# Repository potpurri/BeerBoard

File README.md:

# BeerBoard

**BeerBoard** is a beer-shaped microcontroller breakout board based on the STM32F030C6T6. [Schematic can be found here.](https://github.com/potpurri/BeerBoard/blob/a81b2d54139fa46588d7e338071e49ddc263d606/Schematic_v02.pdf) Originally designed as a trophy for a beer quiz, its primary feature is blinking LEDs, adding a fun, interactive element to the prize. The project also served as an opportunity to experiment with JLCPCB's multicolor silkscreen options.

This board consists of **4 layers**, providing a robust platform for various applications beyond its original purpose. It also includes **breakout pins for I2C, SPI, and USART**, offering versatile connectivity options for external devices and peripherals. Below are images showing the assebled board, different silkscreen options and 3D renderings of the BeerBoard.

The board is soldered by me using a [Pinecil V2](https://wiki.pine64.org/wiki/Pinecil) by PINE64  and [MHP50](https://e-design.com.cn/en/Mini-Hot-Plate-Preheater-MHP50-PG9555615) by MiniWare.

## Features
- Beer-shaped PCB design
- STM32F030C6T6 microcontroller at its core
- Blinking LEDs for visual effects
- 4-layer PCB
- Available in both multicolor and regular silkscreen versions

## Images

### Assembled board

### PCBs

### 3D Renderings & Schematic

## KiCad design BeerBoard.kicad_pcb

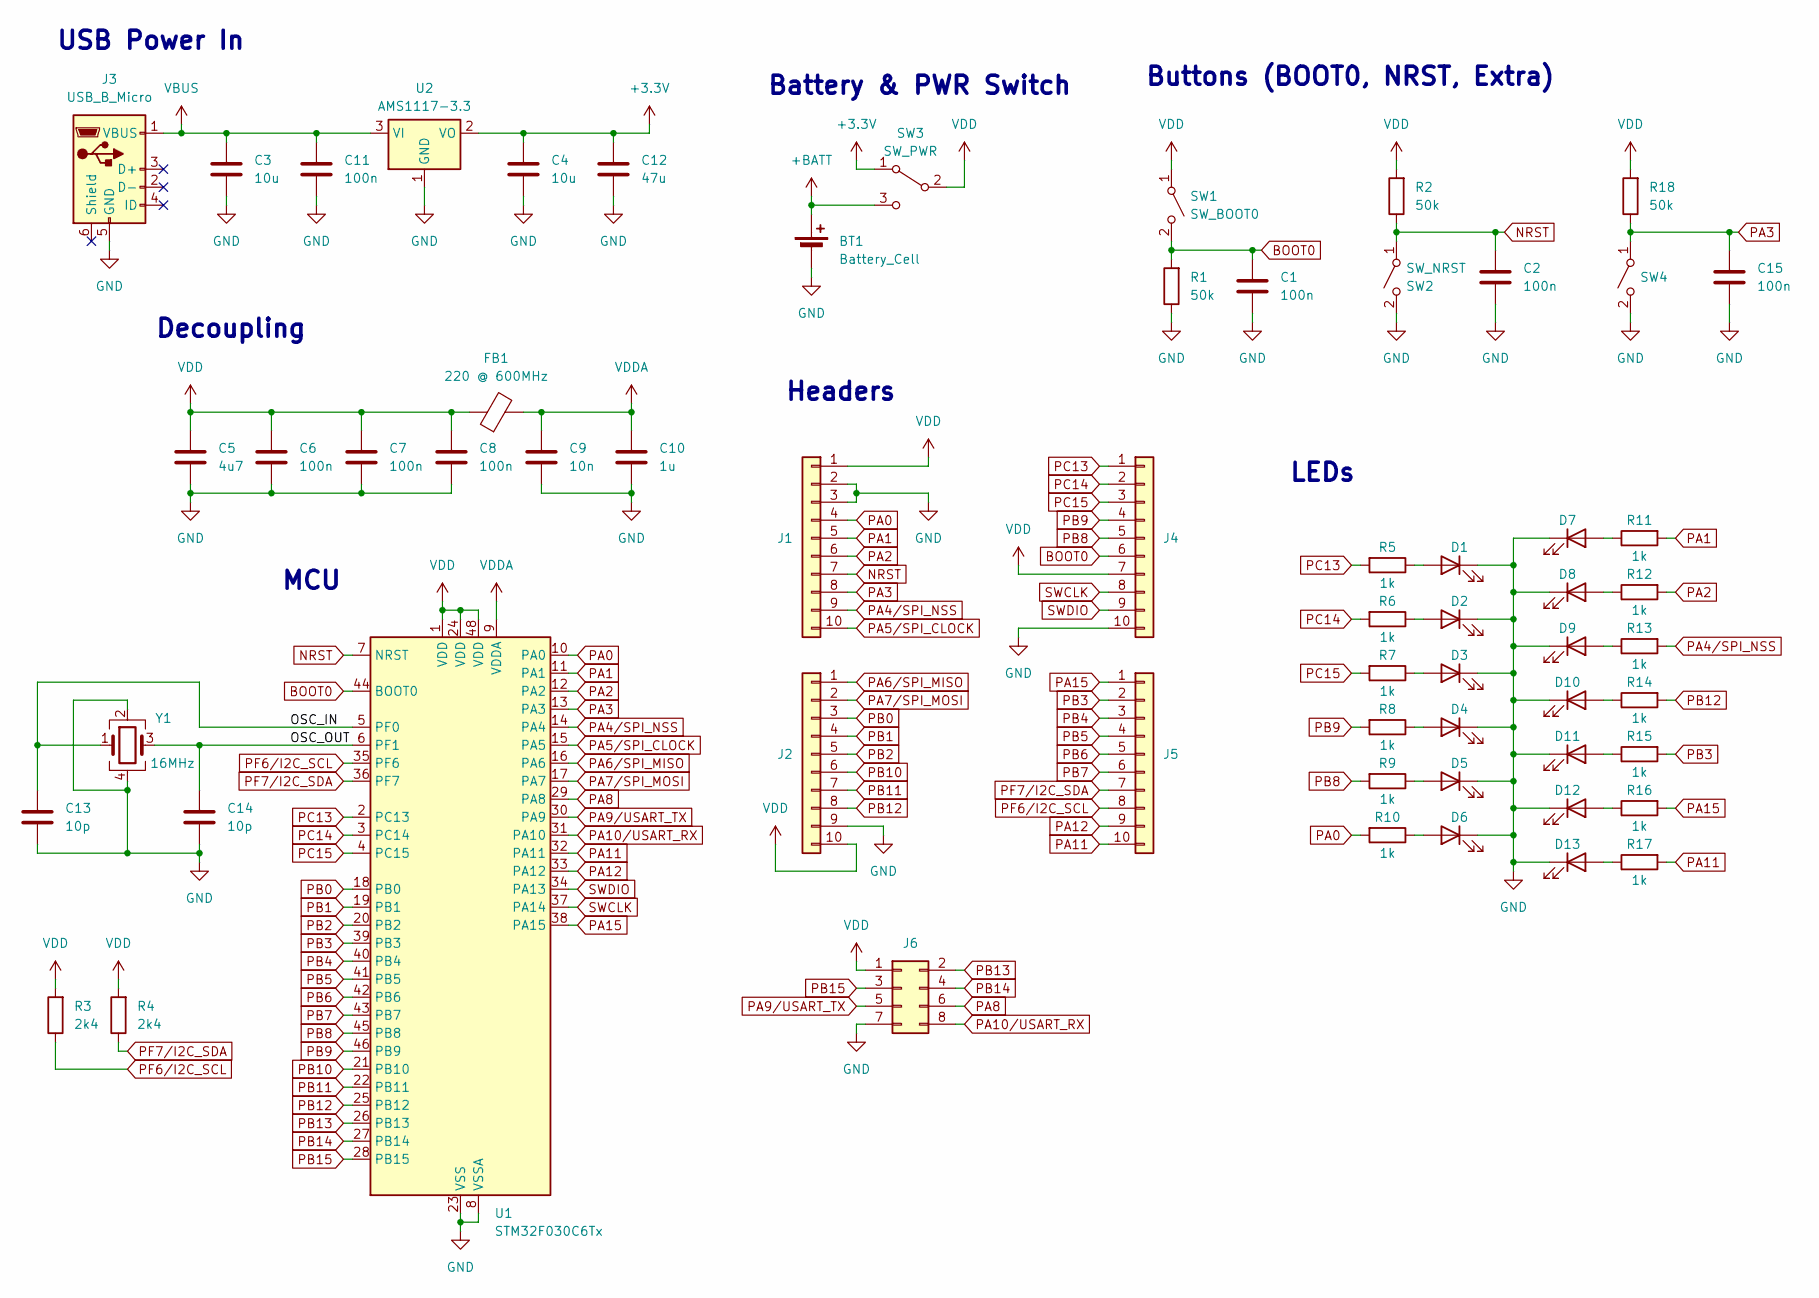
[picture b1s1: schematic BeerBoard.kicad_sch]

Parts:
BT1: Battery_Cell; CoinCell CR2032
C1, C2, C6, C7, C8, C11, C15: 100n; C_0603_1608Metric
C3, C4: 10u; C_0805_2012Metric
C5: 4u7; C_0805_2012Metric
C9: 10n; C_0603_1608Metric
C10: 1u; C_0805_2012Metric
C12: 47u; C_1206_3216Metric
C13, C14: 10p; C_0603_1608Metric
D1, D2, D3, D4, D5, D6, D7, D8, D9, D10, D11, D12, D13: LED; LED_0805_2012Metric_Pad1.15x1.40mm_HandSolder
FB1: 220 @ 600MHz; L_0805_2012Metric
J1, J2, J4, J5: Conn_01x10; PinHeader_1x10_P2.54mm_Vertical
J3: USB_B_Micro; USB_Micro-B_Wuerth_629105150521
J6: Conn_02x04_Odd_Even; PinHeader_2x04_P2.54mm_Vertical
R1, R2, R18: 50k; R_0805_2012Metric
R3, R4: 2k4; R_0805_2012Metric
R5, R6, R7, R8, R9, R10, R11, R12, R13, R14, R15, R16, R17: 1k; R_0603_1608Metric
SW1: SW_BOOT0; 3mm x 4mm micro switch button
SW2, SW4: SW_NRST; 3mm x 4mm micro switch button
SW3: SW_PWR; Schiebeschalter SS-12D00
U1: STM32F030C6Tx; LQFP-48_7x7mm_P0.5mm
U2: AMS1117-3.3; SOT-223-3_TabPin2
Y1: 16MHz; Crystal_SMD_3225-4Pin_3.2x2.5mm

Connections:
+3.3V: C4.1, C12.1, SW3.1 (A), U2.2 (VO)
+BATT: BT1.1 (+), SW3.3 (C)
/OSC_IN: C13.1, U1.5 (PF0), Y1.1
/OSC_OUT: C14.1, U1.6 (PF1), Y1.3
BOOT0: C1.1, J4.6, R1.2, SW1.2 (B), U1.44 (BOOT0)
GND: BT1.2 (-), C1.2, C2.2, C3.2, C4.2, C5.2, C6.2, C7.2, C8.2, C9.2, C10.2, C11.2, C12.2, C13.2, C14.2, C15.2, D1.1 (K), D2.1 (K), D3.1 (K), D4.1 (K), D5.1 (K), D6.1 (K), D7.1 (K), D8.1 (K), D9.1 (K), D10.1 (K), D11.1 (K), D12.1 (K), D13.1 (K), J1.2, J1.3, J2.9, J3.5 (GND), J4.10, J6.7, R1.1, SW2.2 (B), SW4.2 (B), U1.8 (VSSA), U1.23 (VSS), U1.47 (VSS), U2.1 (GND), Y1.2, Y1.4
NRST: C2.1, J1.7, R2.1, SW2.1 (A), U1.7 (NRST)
unnamed: D1.2 (A), R5.1
unnamed: D2.2 (A), R6.1
unnamed: D3.2 (A), R7.1
unnamed: D4.2 (A), R8.1
unnamed: D5.2 (A), R9.1
unnamed: D6.2 (A), R10.1
unnamed: D7.2 (A), R11.1
unnamed: D8.2 (A), R12.1
unnamed: D9.2 (A), R13.1
unnamed: D10.2 (A), R14.1
unnamed: D11.2 (A), R15.1
unnamed: D12.2 (A), R16.1
unnamed: D13.2 (A), R17.1
PA0: J1.4, R10.2, U1.10 (PA0)
PA1: J1.5, R11.2, U1.11 (PA1)
PA2: J1.6, R12.2, U1.12 (PA2)
PA3: C15.1, J1.8, R18.1, SW4.1 (A), U1.13 (PA3)
PA4/SPI_NSS: J1.9, R13.2, U1.14 (PA4)
PA5/SPI_CLOCK: J1.10, U1.15 (PA5)
PA6/SPI_MISO: J2.1, U1.16 (PA6)
PA7/SPI_MOSI: J2.2, U1.17 (PA7)
PA8: J6.6, U1.29 (PA8)
PA9/USART_TX: J6.5, U1.30 (PA9)
PA10/USART_RX: J6.8, U1.31 (PA10)
PA11: J5.10, R17.2, U1.32 (PA11)
PA12: J5.9, U1.33 (PA12)
PA15: J5.1, R16.2, U1.38 (PA15)
PB0: J2.3, U1.18 (PB0)
PB1: J2.4, U1.19 (PB1)
PB2: J2.5, U1.20 (PB2)
PB3: J5.2, R15.2, U1.39 (PB3)
PB4: J5.3, U1.40 (PB4)
PB5: J5.4, U1.41 (PB5)
PB6: J5.5, U1.42 (PB6)
PB7: J5.6, U1.43 (PB7)
PB8: J4.5, R9.2, U1.45 (PB8)
PB9: J4.4, R8.2, U1.46 (PB9)
PB10: J2.6, U1.21 (PB10)
PB11: J2.7, U1.22 (PB11)
PB12: J2.8, R14.2, U1.25 (PB12)
PB13: J6.2, U1.26 (PB13)
PB14: J6.4, U1.27 (PB14)
PB15: J6.3, U1.28 (PB15)
PC13: J4.1, R5.2, U1.2 (PC13)
PC14: J4.2, R6.2, U1.3 (PC14)
PC15: J4.3, R7.2, U1.4 (PC15)
PF6/I2C_SCL: J5.8, R3.1, U1.35 (PF6)
PF7/I2C_SDA: J5.7, R4.1, U1.36 (PF7)
SWCLK: J4.8, U1.37 (PA14)
SWDIO: J4.9, U1.34 (PA13)
VBUS: C3.1, C11.1, J3.1 (VBUS), U2.3 (VI)
VDD: C5.1, C6.1, C7.1, C8.1, FB1.1, J1.1, J2.10, J4.7, J6.1, R2.2, R3.2, R4.2, R18.2, SW1.1 (A), SW3.2 (B), U1.1 (VDD), U1.24 (VDD), U1.48 (VDD)
VDDA: C9.1, C10.1, FB1.2, U1.9 (VDDA)

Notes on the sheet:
MCU
Decoupling
USB Power In
Headers
Buttons (BOOT0, NRST, Extra)
LEDs
Battery & PWR Switch

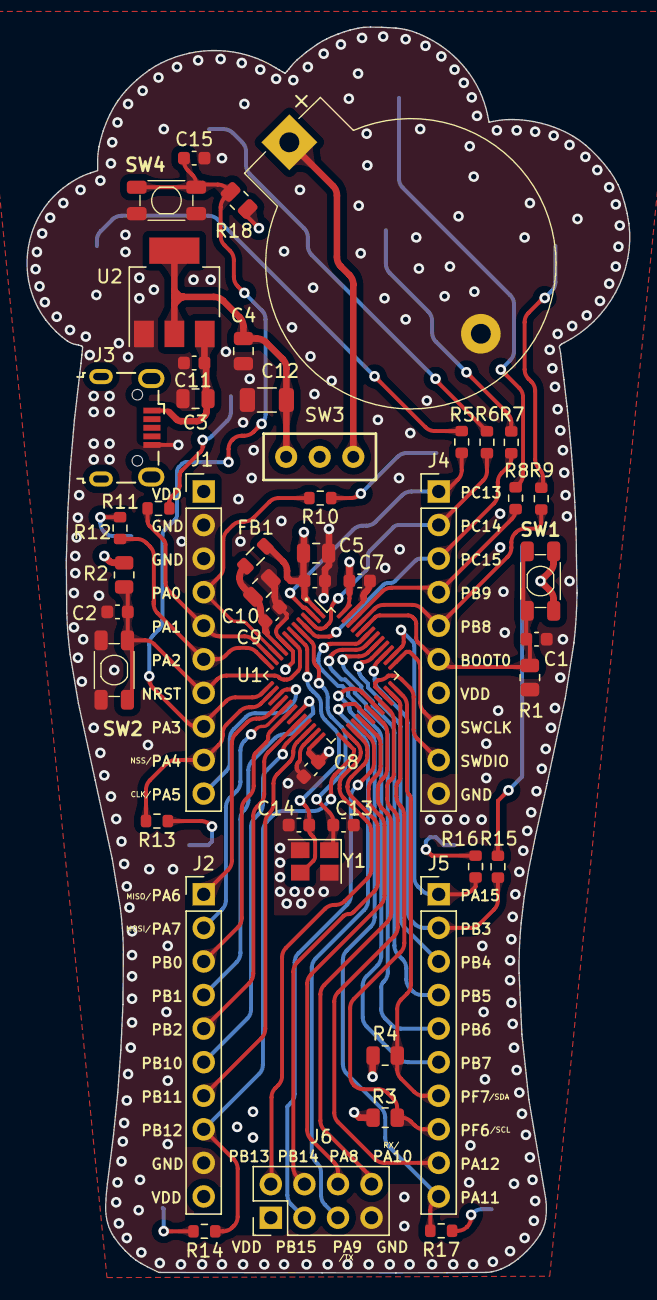
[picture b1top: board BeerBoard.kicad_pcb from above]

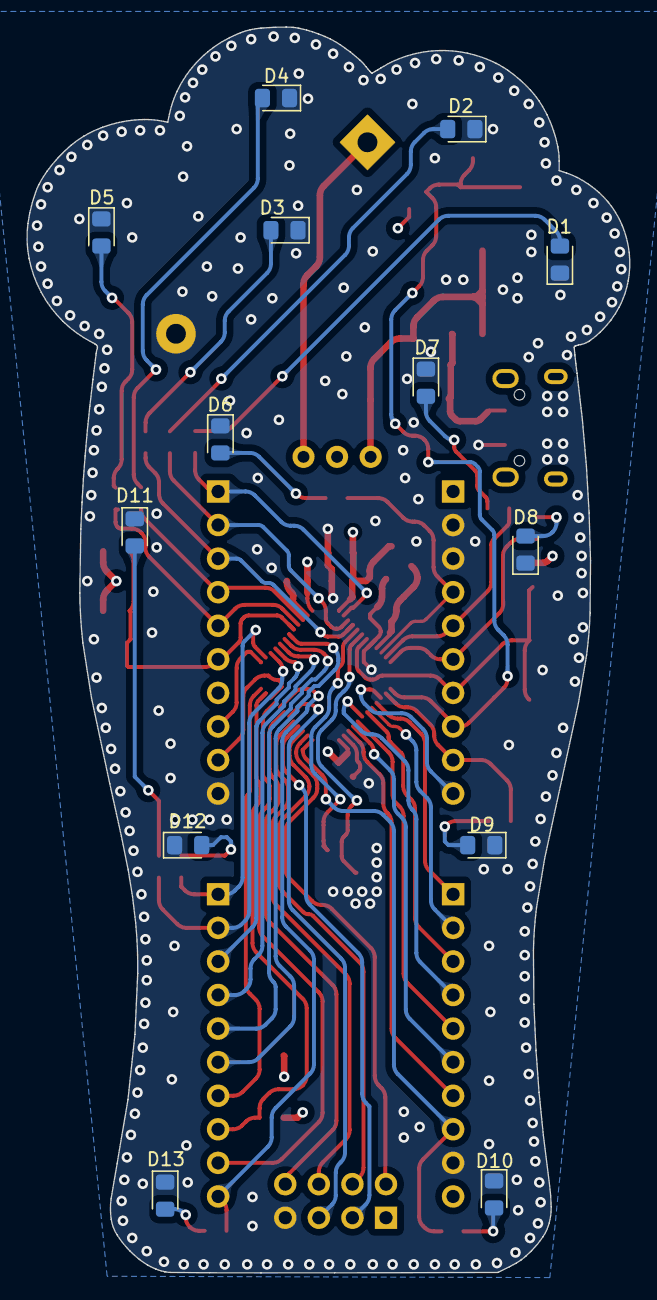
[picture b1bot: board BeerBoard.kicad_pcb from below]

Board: 4 copper layers, 45.6 x 94.3 mm, 61 parts (13 on the bottom side), 60 nets.

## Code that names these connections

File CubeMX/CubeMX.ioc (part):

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Mcu.Name=STM32F030C6Tx
Mcu.Package=LQFP48
Mcu.UserName=STM32F030C6Tx
PA0.GPIOParameters=PinState,GPIO_Label
PA0.GPIO_Label=D6
PA0.PinState=GPIO_PIN_SET
PA0.Signal=GPIO_Output
PA1.GPIOParameters=PinState,GPIO_Label
PA1.GPIO_Label=D7
PA1.PinState=GPIO_PIN_SET
PA1.Signal=GPIO_Output
PA10.GPIOParameters=PinState,GPIO_Label
PA10.GPIO_Label=D2_STND
PA10.PinState=GPIO_PIN_SET
PA10.Signal=GPIO_Output
PA11.GPIOParameters=PinState,GPIO_Label
PA11.GPIO_Label=D13
PA11.PinState=GPIO_PIN_SET
PA11.Signal=GPIO_Output
PA13.Mode=Serial_Wire
PA13.Signal=SYS_SWDIO
PA14.Mode=Serial_Wire
PA14.Signal=SYS_SWCLK
PA15.GPIOParameters=PinState,GPIO_Label
PA15.GPIO_Label=D12
PA15.PinState=GPIO_PIN_SET
PA15.Signal=GPIO_Output
PA2.GPIOParameters=PinState,GPIO_Label
PA2.GPIO_Label=D8
PA2.PinState=GPIO_PIN_SET
PA2.Signal=GPIO_Output
PA4.GPIOParameters=PinState,GPIO_Label
PA4.GPIO_Label=D9
PA4.PinState=GPIO_PIN_SET
PA4.Signal=GPIO_Output
PA5.Mode=Full_Duplex_Master
PA5.Signal=SPI1_SCK
PA6.Mode=Full_Duplex_Master
PA6.Signal=SPI1_MISO
PA7.Mode=Full_Duplex_Master
PA7.Signal=SPI1_MOSI
PA8.GPIOParameters=PinState,GPIO_Label
PA8.GPIO_Label=D1_STND
PA8.PinState=GPIO_PIN_SET
PA8.Signal=GPIO_Output
PA9.GPIOParameters=PinState,GPIO_Label
PA9.GPIO_Label=D3_STND
PA9.PinState=GPIO_PIN_SET
PA9.Signal=GPIO_Output
PB12.GPIOParameters=PinState,GPIO_Label
PB12.GPIO_Label=D10
PB12.PinState=GPIO_PIN_SET
PB12.Signal=GPIO_Output
PB13.GPIOParameters=PinState,GPIO_Label
PB13.GPIO_Label=D5_STND
PB13.PinState=GPIO_PIN_SET
PB13.Signal=GPIO_Output
PB14.GPIOParameters=GPIO_PuPd,GPIO_Label
PB14.GPIO_Label=STND_CONNECTED
PB14.GPIO_PuPd=GPIO_PULLDOWN
PB14.Signal=GPIO_Input
PB15.GPIOParameters=PinState,GPIO_Label
PB15.GPIO_Label=D4_STND
PB15.PinState=GPIO_PIN_SET
PB15.Signal=GPIO_Output
PB3.GPIOParameters=PinState,GPIO_Label
PB3.GPIO_Label=D11
PB3.PinState=GPIO_PIN_SET
PB3.Signal=GPIO_Output
PB8.GPIOParameters=PinState,GPIO_Label
PB8.GPIO_Label=D5
PB8.PinState=GPIO_PIN_SET
PB8.Signal=GPIO_Output
PB9.GPIOParameters=PinState,GPIO_Label
PB9.GPIO_Label=D4
PB9.PinState=GPIO_PIN_SET
PB9.Signal=GPIO_Output
PC13.GPIOParameters=PinState,GPIO_Label
PC13.GPIO_Label=D1
PC13.PinState=GPIO_PIN_SET
PC13.Signal=GPIO_Output
PC14-OSC32_IN.GPIOParameters=PinState,GPIO_Label
PC14-OSC32_IN.GPIO_Label=D2
PC14-OSC32_IN.PinState=GPIO_PIN_SET
PC14-OSC32_IN.Signal=GPIO_Output
PC15-OSC32_OUT.GPIOParameters=PinState,GPIO_Label
PC15-OSC32_OUT.GPIO_Label=D3
PC15-OSC32_OUT.PinState=GPIO_PIN_SET
PC15-OSC32_OUT.Signal=GPIO_Output
PF0-OSC_IN.Mode=HSE-External-Oscillator
PF0-OSC_IN.Signal=RCC_OSC_IN
PF1-OSC_OUT.Mode=HSE-External-Oscillator
PF1-OSC_OUT.Signal=RCC_OSC_OUT
PF6.Mode=I2C
PF6.Signal=I2C1_SCL
PF7.Mode=I2C
PF7.Signal=I2C1_SDA
board=custom

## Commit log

2024-06-07 created folder for old schematics
2024-06-07 rm v01.pdf
2024-06-08 v0.2 - ready for manufactoring
2024-09-08 version 0.2
2024-09-08 added images
2024-09-08 minor readme updates
2024-09-08 added soldering to readme
